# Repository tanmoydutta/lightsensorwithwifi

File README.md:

<h1>ESP32-C3 based Light sensor</h1>

<h2>Description</h2>
This tiny module is designed around Espressief's ESP32-C3 System On a Chip. Purpose of this module is simple, measure the ambient or incident
light and communicate the reading through the chip's built-in WiFi interface. It uses AMS OSRAM TSL2591 sensor to measure the incident light.

Primary challenge has been to design an RF (Radio Frequency) optimised PCB (Printed Circuit Board) to accommodate this electronics. This designed is optimised for WiFi 2.4GHz and features a
chip antenna (Ignion's NN01-102) to minimize the board size (35mm x 20mm).

The PCB has been designed as per the hardware design guidelines from Espressief with one noticeable deviation on the thickness of the PCB (1.6mm instead of the recommended ~0.8mm)

RF part of the board has been tested with a VNA (Vector Network Analyser) and has been optimized with the help of a matching Pi-network. 
Antenna traces are also designed based upon the datasheet specification and recommended trace pattern.

This hardware has been certified with Open Source Hardware Association

<h2>The Module</h2>
End result of the PCB is a 4 layer design and manufactured with the help of JLC PCB (https://jlcpcb.com) which according to their documentation has a 
dielectric constant of 4.5 for FR-4 type material. 

The light sensor is mounted on the back side of the board as depicted below -

Here is a size reference for the end module - 

<h2>Enclosure</h2>
I went ahead and also designed a 3D model for the housing of this module for application - 

<h2>Programming</h2>
Add your own firmware and code to make use of the built-in sensor and indicator. This module can be programmed using Arduino or ESP-IDF IDE. This module has a 
close resemblance with LOLIN C3 Mini or Adafruit C3 QTPy, hence those core board definitions are compatible with this module.

<h2>Design and Architecture</h2>
Below is the System Context for this module highlighting 
the interfaces and interactions with this module. 

Also a blown up building block of functionality within.

<h2>Applications</h2>
One implementation that I personally use this module is for the purpose of controlling the lights on my balcony and eventually also festive lights during Christmas.
Following a possible application diagram -

<h2>Open Source Hardware</h2>
This board is an OSHWA approved design: <a href="https://certification.oshwa.org/nl000015.html">NL000015</a>

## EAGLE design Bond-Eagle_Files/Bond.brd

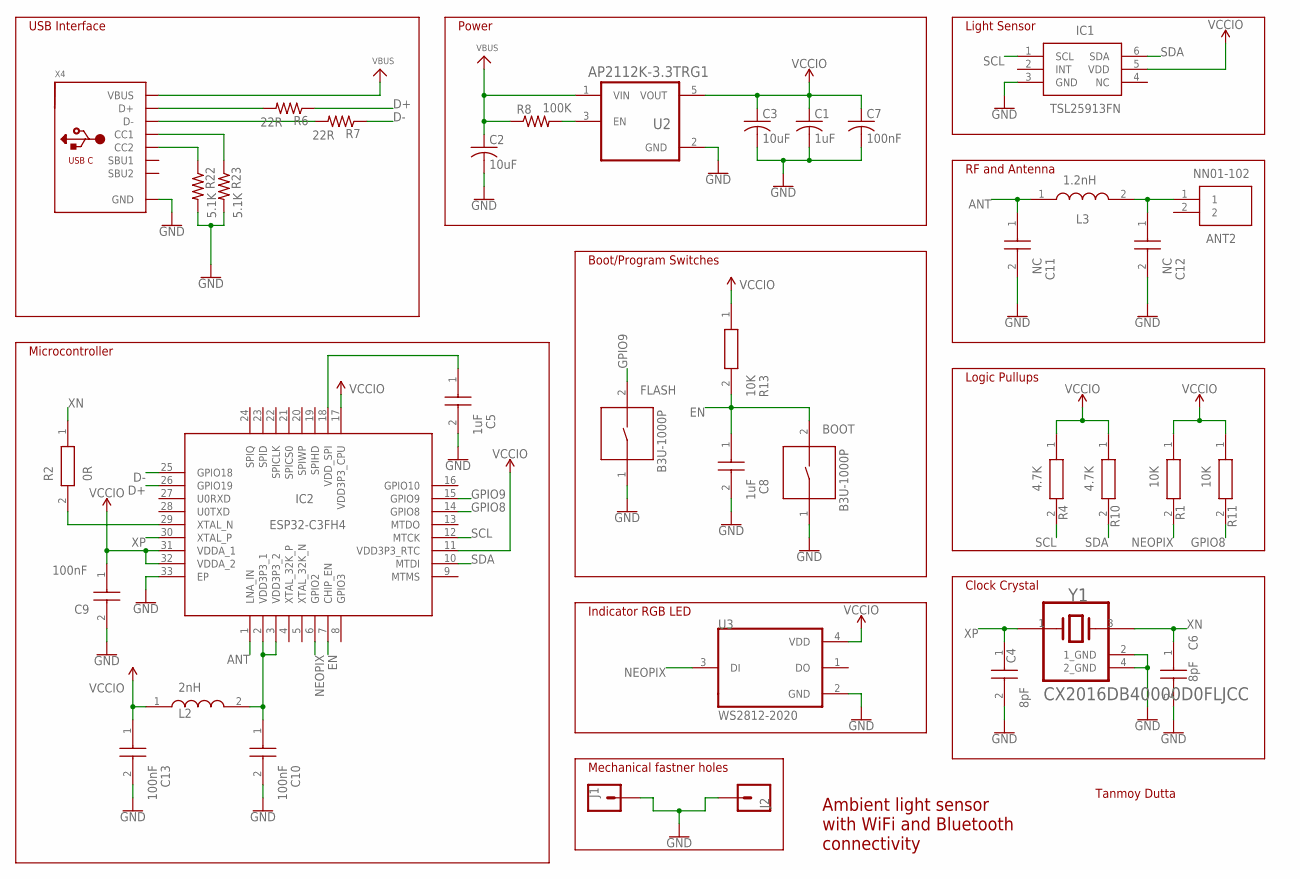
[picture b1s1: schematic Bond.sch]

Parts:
ANT2: NN01-102; NN01102
BOOT: B3U-1000P; SW_B3U-1000P
C1: 1uF; C0402
C2, C3: 10uF; C0402
C4, C6: 8pF; CAPC1005X55N
C5, C8: 1uF; CAPC1005X55N
C7: 100nF; C0402
C9, C10, C13: 100nF; CAPC1005X55N
C11, C12: NC; CAPC1005X55N
FLASH: B3U-1000P; SW_B3U-1000P
IC1: TSL25913FN
IC2: ESP32-C3FH4; QFN50P500X500X90-33N
J1, J2: CONN_01PTH_2MM; 1X01_2MM
L2: 2nH; LQG15WH0N7B02D
L3: 1.2nH; LQW15CNR20J00B
R1, R11, R13: 10K; RESC1005X40N
R2: 0R; RESC1005X40N
R4, R10: 4.7K; RESC1005X40N
R6, R7: 22R; R0402
R8: 100K; R0402
R22, R23: 5.1K; R0402
U2: AP2112K-3.3TRG1; SOT95P285X140-5N
U3: WS2812-2020; LED_WS2812-2020
X4: MICROBUILDER_USB_C; MICROBUILDER_USB_C_CUSB31-CFM2AX-01-X
Y1: 40MHz; KYOCERA_INTERNATIONAL_INC._ELECTRONIC_COMPONENTS_CX2016DB40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

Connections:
ANT: C11.1, IC2.1 (LNA_IN), L3.1
D+: IC2.26 (GPIO19), R6.1
D-: IC2.25 (GPIO18), R7.1
EN: BOOT.2, C8.1, IC2.7 (CHIP_EN), R13.2
GND: BOOT.1, C1.2, C2.2, C3.2, C4.2, C5.2, C6.2, C7.2, C8.2, C9.2, C10.2, C11.2, C12.2, C13.2, FLASH.1, IC1.3 (GND), IC2.33 (EP), J1.1, J2.1, R22.2, R23.2, U2.2 (GND), U3.2 (GND), X4.A1B12 (GND), X4.B1A12 (GND), Y1.2 (1_GND), Y1.4 (2_GND)
GPIO8: IC2.14 (GPIO8), R11.2
GPIO9: FLASH.2, IC2.15 (GPIO9)
unnamed: C5.1, IC2.18 (VDD_SPI)
unnamed: ANT2.1, C12.1, L3.2
unnamed: C10.1, IC2.2 (VDD3P3_1), IC2.3 (VDD3P3_2), L2.2
unnamed: IC2.29 (XTAL_N), R2.2
unnamed: R22.1, X4.B5 (CC2)
unnamed: R23.1, X4.A5 (CC1)
unnamed: R7.2, X4.A7 (D-), X4.B7 (D-)
unnamed: R6.2, X4.A6 (D+), X4.B6 (D+)
unnamed: R8.2, U2.3 (EN)
NEOPIX: IC2.6 (GPIO2), R1.2, U3.3 (DI)
SCL: IC1.1 (SCL), IC2.12 (MTCK), R4.2
SDA: IC1.6 (SDA), IC2.10 (MTDI), R10.2
VBUS: C2.1, R8.1, U2.1 (VIN), X4.A4B9 (VBUS), X4.B4A9 (VBUS)
VCCIO: C1.1, C3.1, C7.1, C9.1, C13.1, IC1.5 (VDD), IC2.11 (VDD3P3_RTC), IC2.17 (VDD3P3_CPU), IC2.31 (VDDA_1), IC2.32 (VDDA_2), L2.1, R1.1, R4.1, R10.1, R11.1, R13.1, U2.5 (VOUT), U3.4 (VDD)
XN: C6.1, R2.1, Y1.3
XP: C4.1, IC2.30 (XTAL_P), Y1.1

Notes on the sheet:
Microcontroller
USB Interface
Power
Boot/Program Switches
Light Sensor
RF and Antenna
Indicator RGB LED
Mechanical fastner holes
Clock Crystal
Logic Pullups
Ambient light sensor with WiFi and Bluetooth connectivity
Tanmoy Dutta

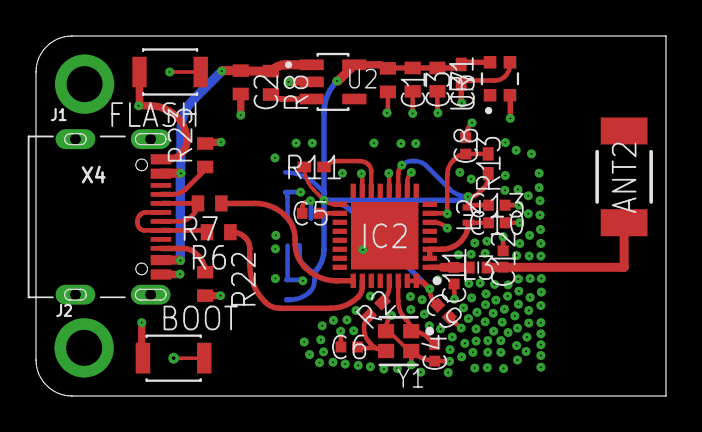
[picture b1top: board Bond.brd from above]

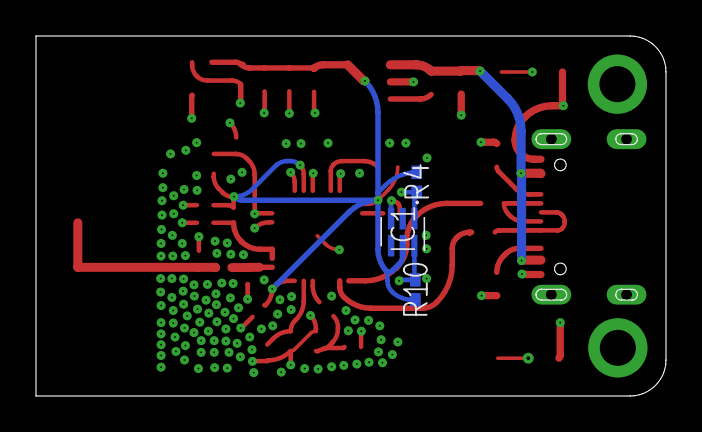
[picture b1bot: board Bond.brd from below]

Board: 4 copper layers, 35.0 x 20.0 mm, 37 parts (3 on the bottom side), 23 nets.

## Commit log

2023-09-21 Adding Bond files
2023-09-21 Adding Bond in enclosure image
2023-09-21 Update README.md
    First documentation with images
2023-09-21 Image size adjusted
2023-09-21 Update README.md
    Added further details
2023-09-21 System Architecture and aplication diagrams
2023-09-21 Update README.md
    Updated additional info and created sections
2023-09-21 Updated the Building block diagram
2023-09-21 Adding Sensor slot image
2023-09-21 Update README.md
    Added image
2023-09-26 Adding correct 3D file for the PCB
2023-09-27 Update README.md
    Added OSHWA certification link
2023-09-27 Adding a sample source code to operate the unit
2023-09-27 Adding OSHWA certificate mark
2023-09-27 Update README.md
    Adding OSHWA Certificate
2023-09-27 Update README.md
    Adjusting broken link

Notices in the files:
parts and their libraries:
SparkFun-Connectors: Licensing: Creative Commons ShareAlike 4.0 International - https://creativecommons.org/licenses/by-sa/4.0
